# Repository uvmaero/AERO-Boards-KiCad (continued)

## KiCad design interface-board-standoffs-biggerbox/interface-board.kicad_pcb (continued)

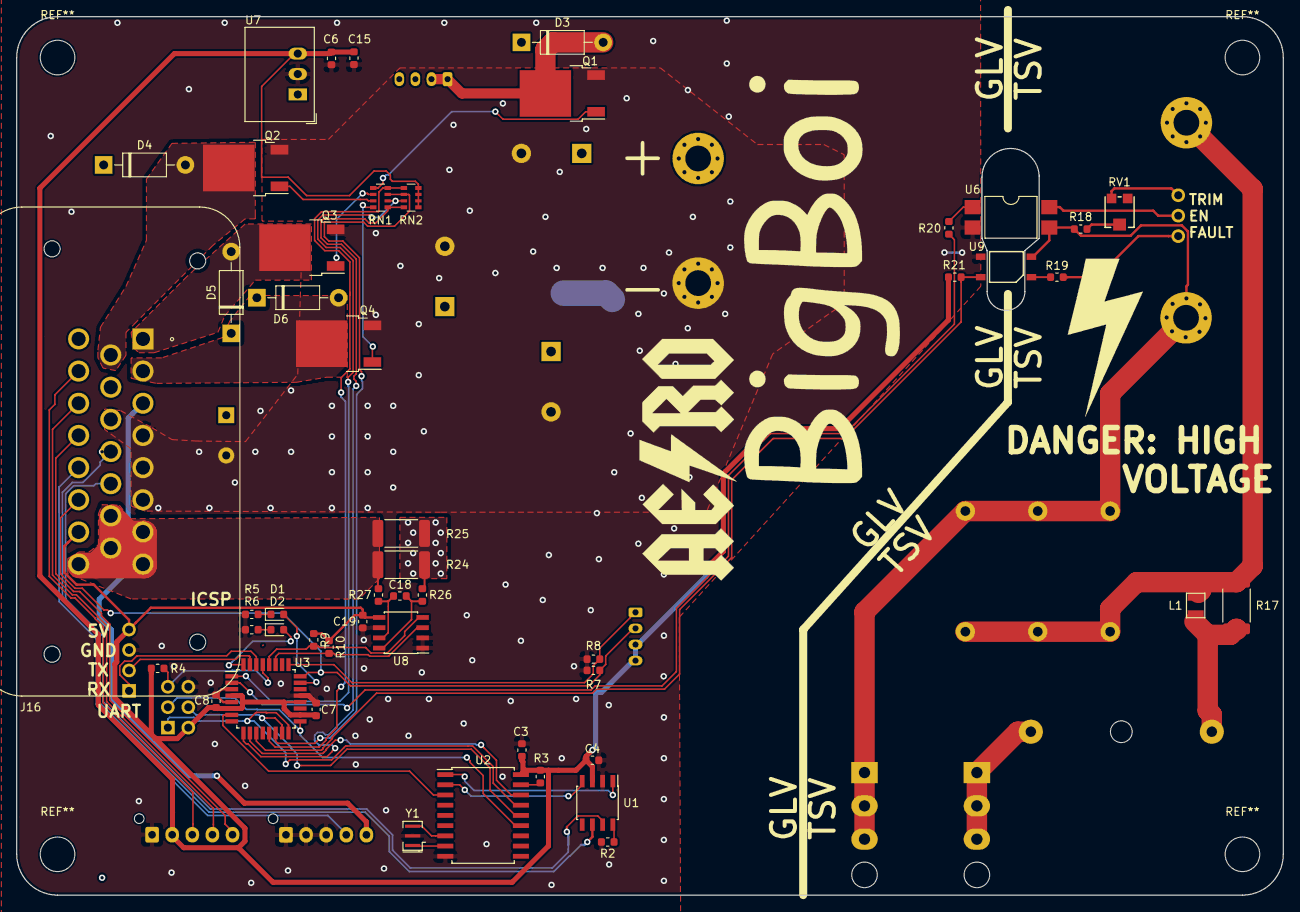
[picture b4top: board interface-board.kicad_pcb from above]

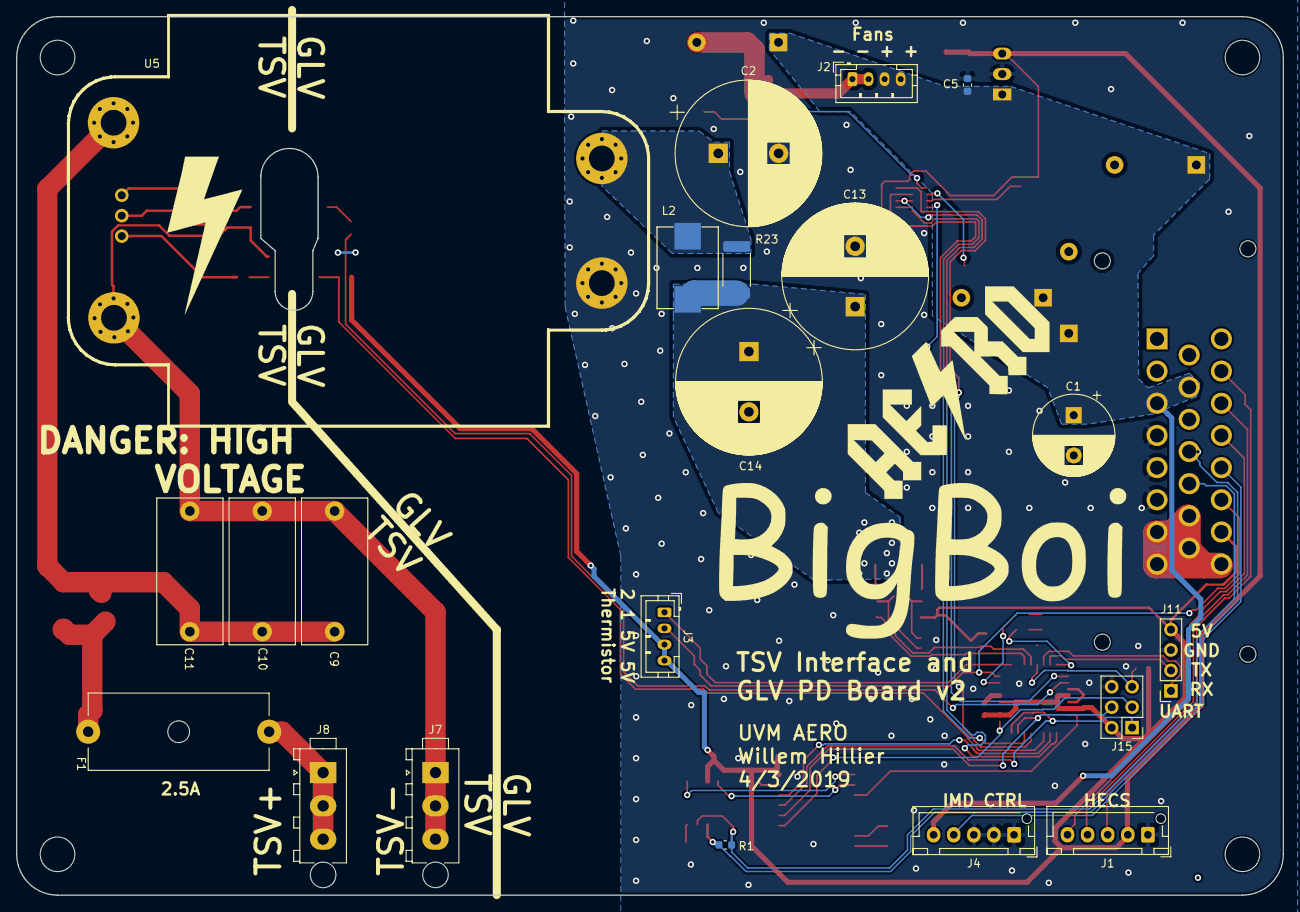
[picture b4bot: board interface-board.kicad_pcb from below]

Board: 2 copper layers, 157.5 x 109.2 mm, 70 parts (21 on the bottom side), 60 nets.

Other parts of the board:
C1: 470uF; CP_Radial_D10.0mm_P5.00mm
C2, C13: 4700uF; CP_Radial_D18.0mm_P7.50mm
R9, R10: 10k; R_0603_1608Metric

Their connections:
+5V: R9.1, R10.1; also elsewhere on the board
+12V: C1.1; also elsewhere on the board
/Main/sheet5C830478/12V_OUT: C13.1; also elsewhere on the board
GND: C1.2, C2.2, C13.2; also elsewhere on the board
unnamed 39: C2.1; also elsewhere on the board
SCL: R9.2; also elsewhere on the board
SDA: R10.2; also elsewhere on the board

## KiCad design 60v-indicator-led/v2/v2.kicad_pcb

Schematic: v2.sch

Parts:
D1: RED_LED; LPA-C011301S-x LED 0805 LIGHT PIPE SINGLE VERT SMD
J1, J2: Conn_01x02; TE_MATE-N-LOK_1-770866-x_1x02_P4.14mm_Vertical
R1, R2, R3, R4, R5, R6, R7, R8, R9, R10: 1k; R_0805_2012Metric

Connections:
unnamed: D1.1 (K), R10.1
unnamed: D1.2 (A), R9.1
unnamed: J1.1, J1.2, R1.2
unnamed: J2.1, J2.2, R2.2
unnamed: R1.1, R3.2
unnamed: R2.1, R4.2
unnamed: R3.1, R5.2
unnamed: R4.1, R6.2
unnamed: R5.1, R7.2
unnamed: R6.1, R8.2
unnamed: R7.1, R9.2
unnamed: R8.1, R10.2

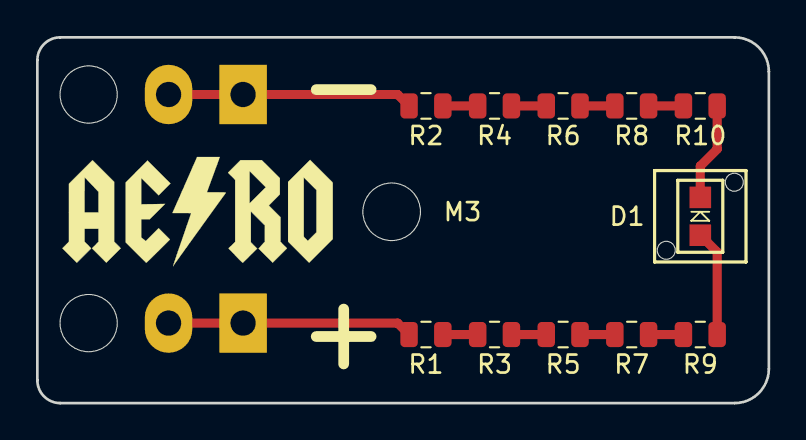
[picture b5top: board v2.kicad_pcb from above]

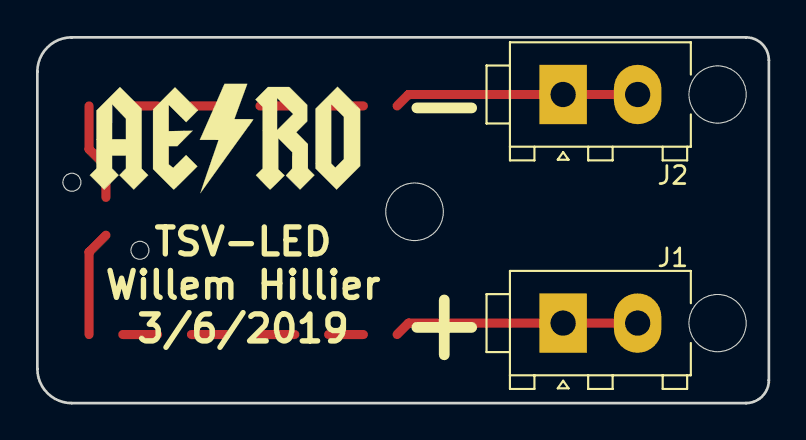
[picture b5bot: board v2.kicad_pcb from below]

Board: 2 copper layers, 40.6 x 20.3 mm, 14 parts (2 on the bottom side), 12 nets.

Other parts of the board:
M3: MountingHole_3.2mm_M3_DIN965

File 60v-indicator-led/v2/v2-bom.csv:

"Id";"Designator";"Package";"Quantity";"Designation";"Supplier and ref";
1;"G***,G***";"AERO_Logo_15x6mm";2;"LOGO";;;
2;"D1";"LPA-C011301S-x LED 0805 LIGHT PIPE SINGLE VERT SMD";1;"RED_LED";;;
3;"R1,R2,R3,R4,R5,R6,R7,R8,R9,R10";"R_0805_2012Metric";10;"1k";;;
4;"M3";"MountingHole_3.2mm_M3_DIN965";1;"MountingHole_3.2mm_M3_DIN965";;;
5;"J1,J2";"TE_MATE-N-LOK_1-770866-x_1x02_P4.14mm_Vertical";2;"Conn_01x02";;;

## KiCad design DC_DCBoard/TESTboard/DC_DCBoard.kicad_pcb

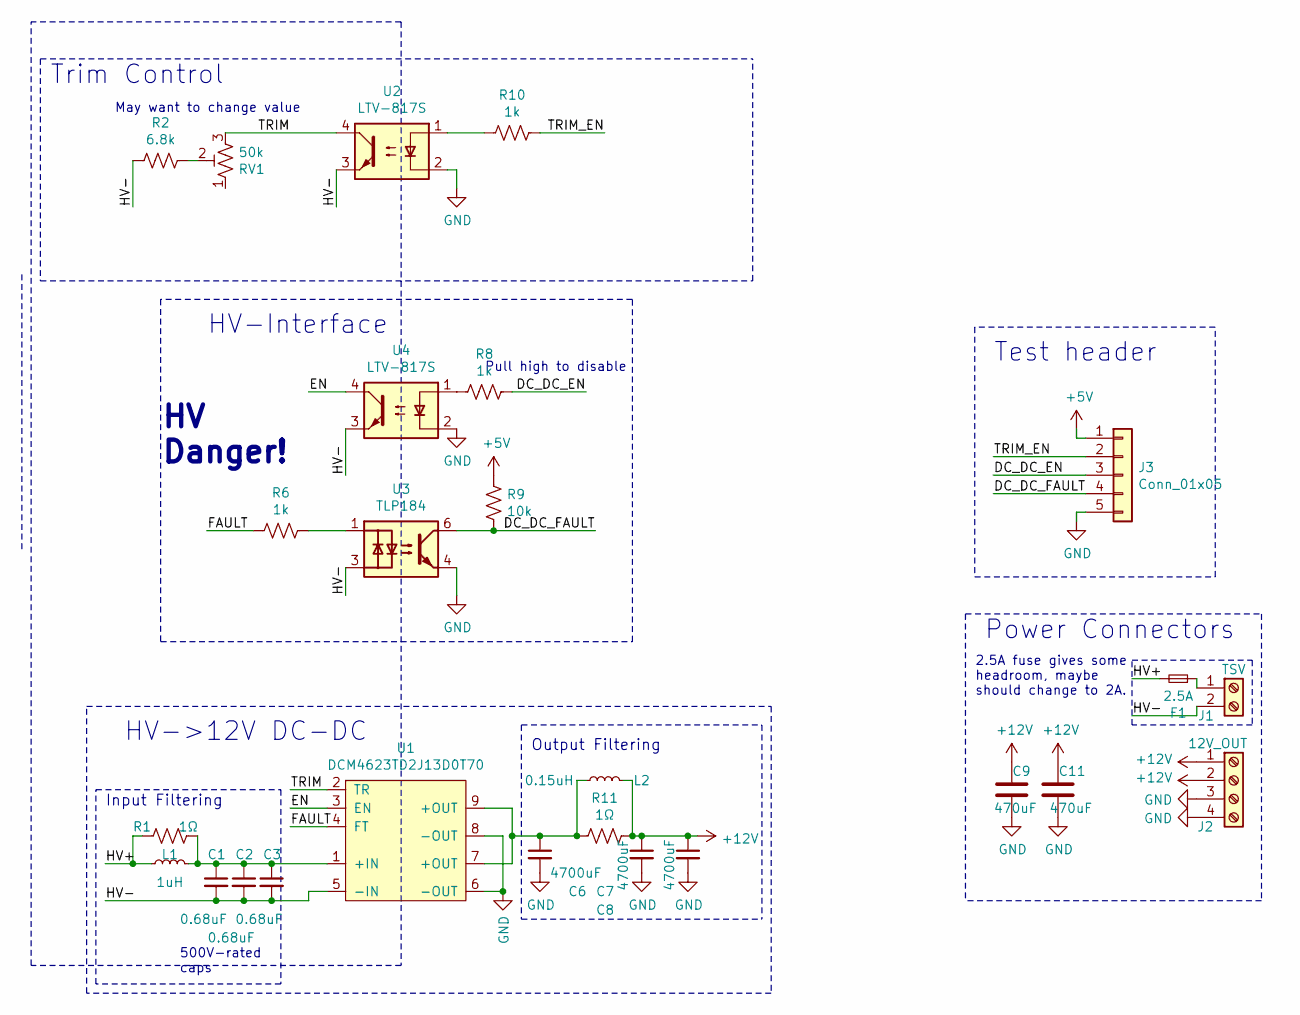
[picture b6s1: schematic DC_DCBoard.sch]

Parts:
C1, C2, C3: 0.68uF; C_Rect_L18.0mm_W8.0mm_P15.00mm_FKS3_FKP3
C6, C7, C8: 4700uF; CP_Radial_D18.0mm_P7.50mm
C9, C11: 470uF; CP_Radial_D10.0mm_P5.00mm
F1: 2.5A; Fuseholder_Cylinder-5x20mm_Schurter_0031_8201_Horizontal_Op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
J1: TSV; TerminalBlock_MetzConnect_Type067_RT01902HDWC_1x02_P10.00mm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
J2: 12V_OUT; TerminalBlock_MetzConnect_Type067_RT01904HDWC_1x04_P10.00mm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
J3: Conn_01x05; PinHeader_1x05_P2.54mm_Vertical
L1: 1uH; Murata_DFE252012P_Inductor
L2: 0.15uH; PA2607
R1, R11: 1Ω; R_2512_6332Metric
R2: 6.8k; R_0603_1608Metric
R6, R8, R10: 1k; R_0603_1608Metric
R9: 10k; R_0603_1608Metric
RV1: 50k; TC33X-503ECT-ND
U1: DCM4623TD2J13D0T70; DCM4623TD2J13D0T70 w_landpattern
U2, U4: LTV-817S; SMDIP-4_W9.53mm
U3: TLP184; TLP182

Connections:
+5V: J3.1, R9.2
+12V: C7.1, C8.1, C9.1, C11.1, J2.1, J2.2, L2.2, R11.1
/DC_DC_EN: J3.3, R8.1
/DC_DC_FAULT: J3.4, R9.1, U3.6
/EN: U1.3 (EN), U4.4
/FAULT: R6.2, U1.4 (FT)
/HV+: F1.2, L1.1, R1.2
/HV-: C1.2, C2.2, C3.2, J1.2, R2.2, U1.5 (-IN), U2.3, U3.3, U4.3
/TRIM: RV1.3, U1.2 (TR), U2.4
/TRIM_EN: J3.2, R10.1
GND: C6.2, C7.2, C8.2, C9.2, C11.2, J2.3, J2.4, J3.5, U1.6 (-OUT), U1.8 (-OUT), U2.2, U3.4, U4.2
unnamed: C1.1, C2.1, C3.1, L1.2, R1.1, U1.1 (+IN)
unnamed: C6.1, L2.1, R11.2, U1.7 (+OUT), U1.9 (+OUT)
unnamed: F1.1, J1.1
unnamed: R2.1, RV1.2
unnamed: R6.1, U3.1
unnamed: R8.2, U4.1
unnamed: R10.2, U2.1

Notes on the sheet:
500V-rated caps
2.5A fuse gives some headroom, maybe should change to 2A.
Input Filtering
Trim Control
Pull high to disable
Power Connectors
HV->12V DC-DC
HV-Interface
HV Danger!
Output Filtering
May want to change value
Test header

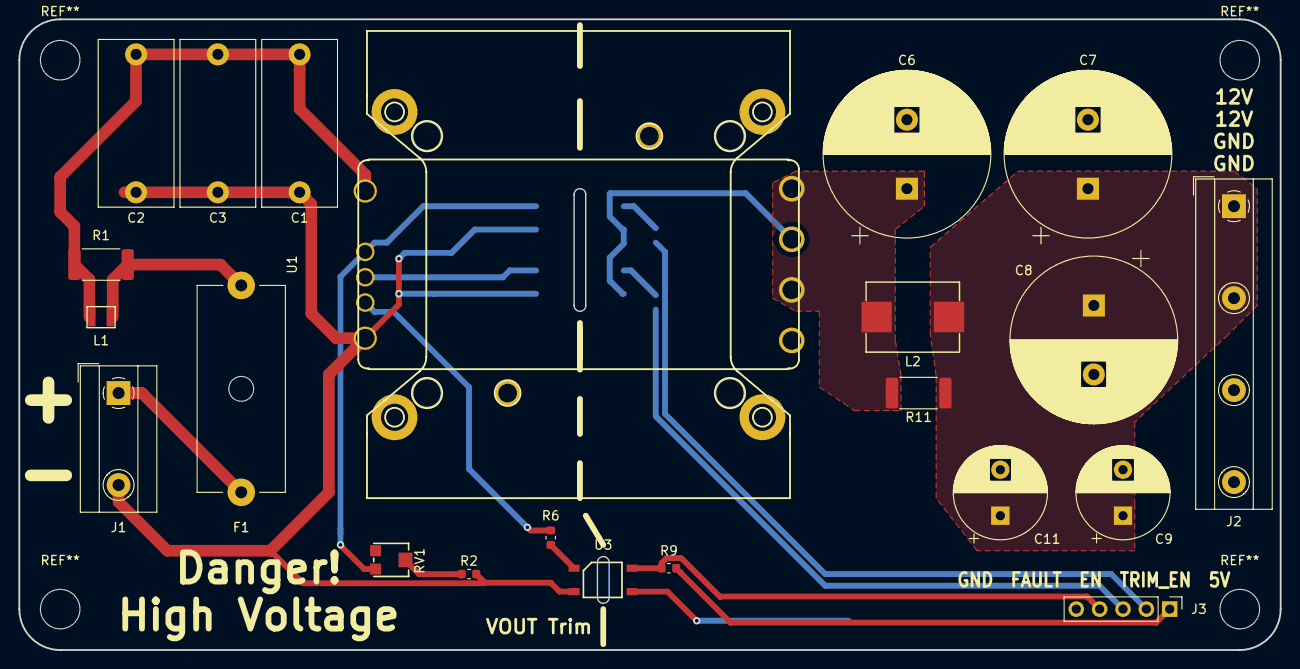
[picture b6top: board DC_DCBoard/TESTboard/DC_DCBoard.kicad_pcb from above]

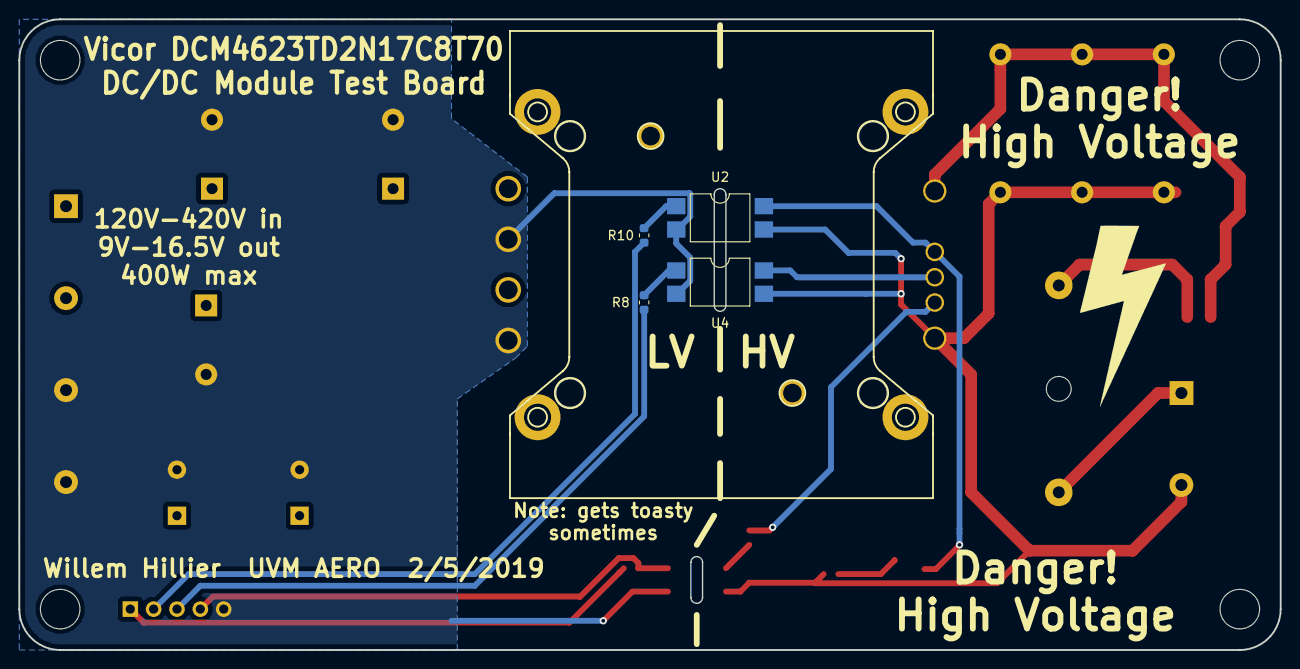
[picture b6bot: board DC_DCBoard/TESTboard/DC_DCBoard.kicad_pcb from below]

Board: 2 copper layers, 137.2 x 68.6 mm, 26 parts (4 on the bottom side), 18 nets.

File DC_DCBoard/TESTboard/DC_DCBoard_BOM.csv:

"Id";"Designator";"Package";"Quantity";"Designation";"Supplier and ref";
1;"F1";"Fuseholder_Cylinder-5x20mm_Schurter_0031_8201_Horizontal_Open_3d";1;"2.5A";;;
2;"U1";"DCM4623TD2J13D0T70_w_landpattern";1;"DCM4623TD2J13D0T70";;;
3;"REF**,REF**,REF**,REF**";"MountingHole_4.3mm_M4";4;"MountingHole_4.3mm_M4";;;
4;"C1,C2,C3";"C_Rect_L18.0mm_W8.0mm_P15.00mm_FKS3_FKP3";3;"0.68uF";;;
5;"C6,C7,C8";"CP_Radial_D18.0mm_P7.50mm";3;"4700uF";;;
6;"C9,C11";"CP_Radial_D10.0mm_P5.00mm";2;"470uF";;;
7;"J1";"TerminalBlock_MetzConnect_Type067_RT01902HDWC_1x02_P10.00mm_Horizontal";1;"TSV";;;
8;"J2";"TerminalBlock_MetzConnect_Type067_RT01904HDWC_1x04_P10.00mm_Horizontal";1;"12V_OUT";;;
9;"L1";"Murata_DFE252012P_Inductor";1;"1uH";;;
10;"L2";"PA2607";1;"0.15uH";;;
11;"R1,R11";"R_2512_6332Metric";2;"1Ω";;;
12;"R6,R8,R10";"R_0603_1608Metric";3;"1k";;;
13;"R9";"R_0603_1608Metric";1;"10k";;;
14;"U2,U4";"SMDIP-4_W9.53mm";2;"LTV-817S";;;
15;"J3";"PinHeader_1x05_P2.54mm_Vertical";1;"Conn_01x05";;;
16;"R2";"R_0603_1608Metric";1;"6.8k";;;
17;"G***";"hvlightningsymbol";1;"LOGO";;;
18;"RV1";"TC33X-503ECT-ND";1;"50k";;;
19;"U3";"TLP182";1;"TLP184";;;

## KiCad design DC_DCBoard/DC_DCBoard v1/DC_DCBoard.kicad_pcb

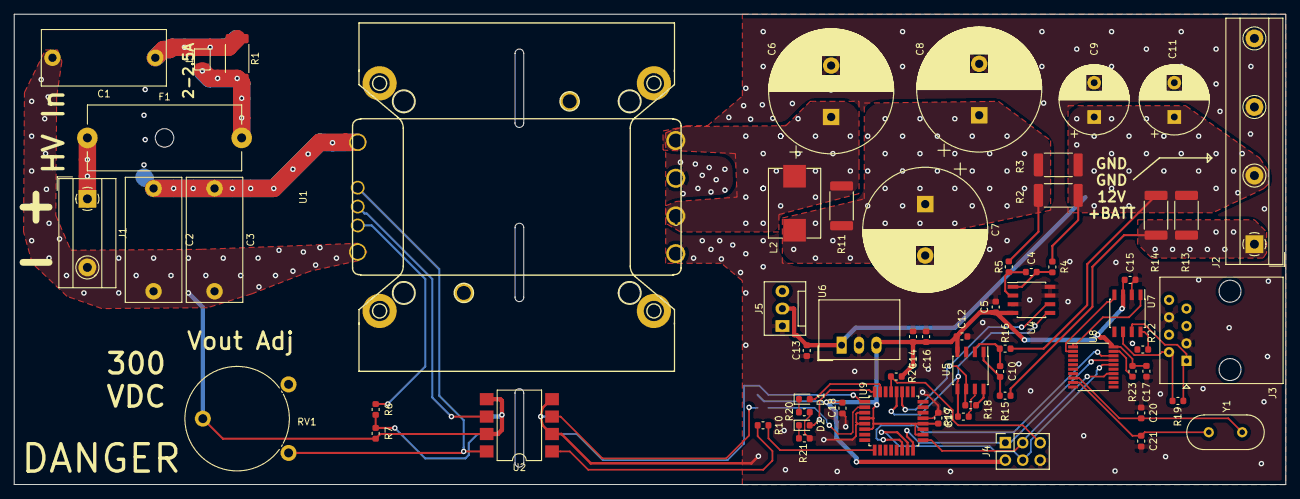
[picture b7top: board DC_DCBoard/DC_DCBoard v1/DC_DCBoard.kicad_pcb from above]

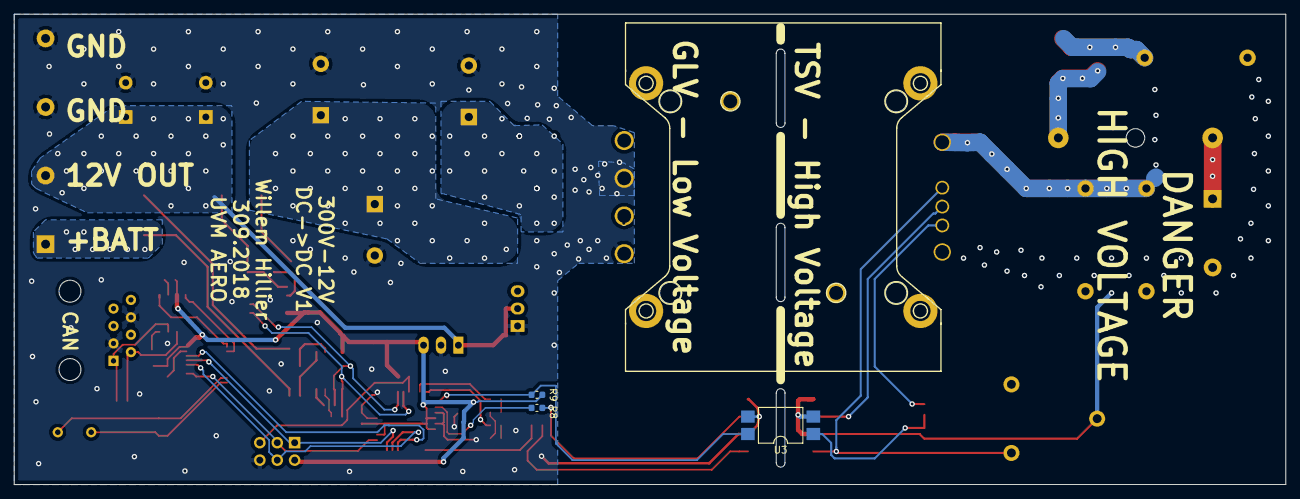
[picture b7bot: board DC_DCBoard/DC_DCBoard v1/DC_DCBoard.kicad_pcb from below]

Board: 2 copper layers, 185.4 x 68.6 mm, 65 parts (3 on the bottom side), 44 nets.

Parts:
C1, C2, C3: 0.68uF; C_Rect_L18.0mm_W8.0mm_P15.00mm_FKS3_FKP3
C4, C5, C10, C12, C14, C15, C17, C18, C19: 0.1uF; C_0603_1608Metric
C6, C7, C8: 4700uF; CP_Radial_D18.0mm_P7.50mm
C9, C11: 470uF; CP_Radial_D10.0mm_P5.00mm
C13, C16: 10uF; C_0603_1608Metric
C20, C21: 22pF; C_0603_1608Metric
D1, D2: LED; LED_0603_1608Metric
F1: 2.5A; Fuseholder_Cylinder-5x20mm_Schurter_0031_8201_Horizontal_Op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
J1: TSV; TerminalBlock_MetzConnect_Type067_RT01902HDWC_1x02_P10.00mm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
J2: 12V_OUT; TerminalBlock_MetzConnect_Type067_RT01904HDWC_1x04_P10.00mm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
J3: RJ45; RJ45_Amphenol_54602-x08_Horizontal
J4: Conn_02x03_Odd_Even; PinSocket_2x03_P2.54mm_Vertical
J5: FAN; FanPinHeader_1x03_P2.54mm_Vertical
L1: 1uH; Murata_DFE252012P_Inductor
L2: 0.15uH; PA2607
R1, R11: 1Ω; R_2512_6332Metric
R2, R3, R13, R14: 0.02; R_2512_6332Metric
R4, R5, R15, R16: 10; R_0603_1608Metric
R6, R8, R10, R20, R21: 1k; R_0603_1608Metric
R7: 50k; R_0603_1608Metric
R9, R17, R18, R22, R23, R24: 10k; R_0603_1608Metric
R19: R_US; R_0603_1608Metric
RV1: 5k; Potentiometer_Piher_PT-15-V02_Vertical
U1: DCM4623TD2J13D0T70; DCM4623TD2J13D0T70 w_landpattern
U2: LTV-827S; SMDIP-8_W9.53mm
U3: LTV-817S; SMDIP-4_W9.53mm
U4, U5: INA219; SOIC-8_3.9x4.9mm_P1.27mm
U6: R-78E5.0-0.5; Converter_DCDC_RECOM_R-78E-0.5_THT
U7: MCP2551-I-SN; SOIC-8_3.9x4.9mm_P1.27mm
U8: MCP2515-IST; TSSOP-20_4.4x6.5mm_P0.65mm
U9: ATmega328P-AU; TQFP-32_7x7mm_P0.8mm
Y1: 16MHz; Crystal_HC49-U_Vertical

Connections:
+5V: C5.2, C12.2, C14.1, C15.1, C16.1, C17.1, C18.1, C19.1, J4.2, R9.2, R23.1, R24.1, U4.4, U5.4, U6.3, U7.3, U8.20, U9.4, U9.6, U9.18, U9.20
+12V: C9.1, C11.1, C13.1, J2.2, J5.2, R2.2, R3.2, R4.2, R13.1, R14.1, R16.2, U6.1
+BATT: J2.1, R13.2, R14.2, R15.2
/12V_UNMETERED: C7.1, C8.1, L2.2, R2.1, R3.1, R5.2, R11.1
/D10: U8.18, U9.14
/DC_DC_EN: R8.1, U9.2
/DC_DC_FAULT: R9.1, U3.4, U9.1
/EN: U1.3, U2.6
/FAULT: R6.2, U1.4
/HV+: F1.2, L1.1, R1.2
/HV-: C1.2, C2.2, C3.2, J1.2, R7.2, RV1.2, U1.5, U2.5, U2.7, U3.2
/LED1: D1.2, U9.31
/LED2: D2.2, U9.32
/MISO: J4.1, U8.17, U9.16
/MOSI: J4.4, U8.16, U9.15
/RESET: J4.5, R24.2, U9.29
/SCK: J4.3, U8.14, U9.17
/SCL: R17.1, U4.5, U5.5, U9.28
/SDA: R18.1, U4.6, U5.6, U9.27
/TRIM: RV1.3, U1.2, U2.8
/TRIM_EN: R10.1, U9.9
GND: C5.1, C6.2, C7.2, C8.2, C9.2, C11.2, C12.1, C13.2, C14.2, C15.2, C16.2, C17.2, C18.2, C19.2, C20.2, C21.2, J2.3, J2.4, J3.3, J3.6, J4.6, J5.1, R20.1, R21.1, R22.2, U1.6, U1.8, U2.2, U2.4, U3.3, U4.3, U4.7, U4.8, U5.3, U6.2, U7.2, U8.10, U9.3, U9.5, U9.21
unnamed: C1.1, C2.1, C3.1, L1.2, R1.1, U1.1
unnamed: C4.1, R4.1, U4.1
unnamed: C4.2, R5.1, U4.2
unnamed: C6.1, L2.1, R11.2, U1.7, U1.9
unnamed: C10.1, R15.1, U5.1
unnamed: C10.2, R16.1, U5.2
unnamed: C20.1, U8.8, Y1.1
unnamed: C21.1, U8.9, Y1.2
unnamed: D1.1, R20.2
unnamed: D2.1, R21.2
unnamed: F1.1, J1.1
unnamed: J3.1, R19.1, U7.7
unnamed: J3.2, R19.2, U7.6
unnamed: R6.1, R7.1, U3.1
unnamed: R8.2, U2.3
unnamed: R10.2, U2.1
unnamed: R17.2, U5.7
unnamed: R18.2, U5.8
unnamed: R22.1, U7.8
unnamed: R23.2, U8.19
unnamed: U7.1, U8.1
unnamed: U7.4, U8.2

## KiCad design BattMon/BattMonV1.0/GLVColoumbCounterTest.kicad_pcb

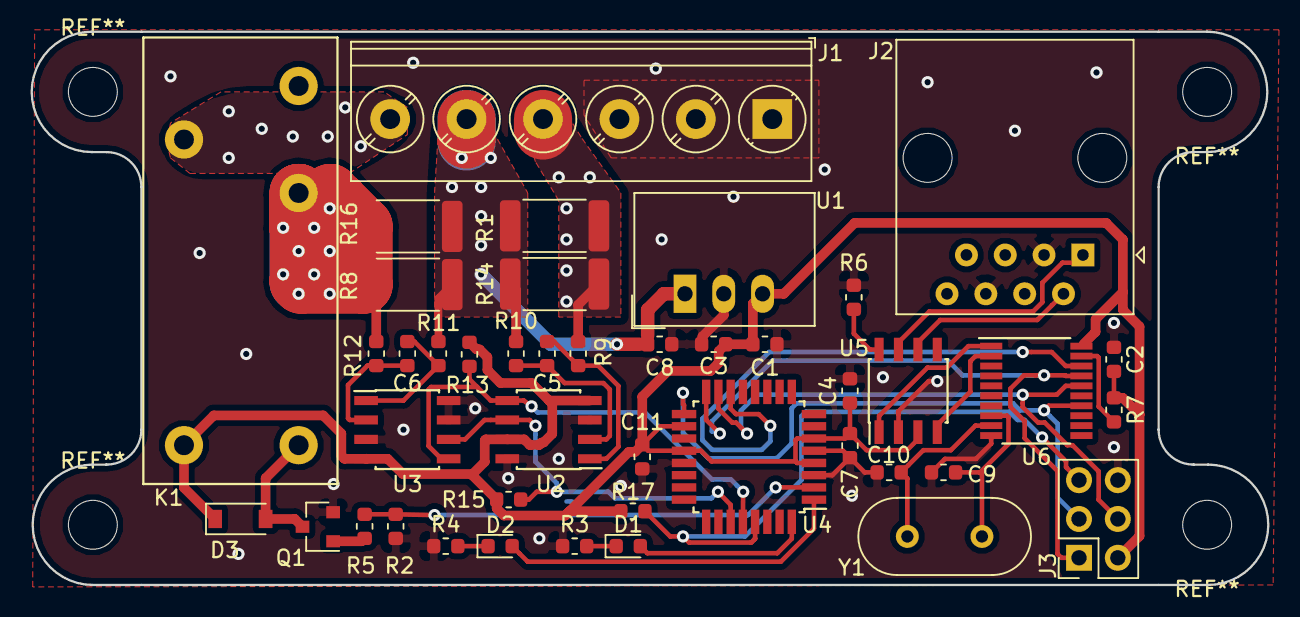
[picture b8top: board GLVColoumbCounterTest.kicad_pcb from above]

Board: 2 copper layers, 80.9 x 36.2 mm, 43 parts (0 on the bottom side), 32 nets.

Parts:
C1, C2, C4, C5, C6, C7, C11: 0.1uF; C_0603_1608Metric
C3, C8: 10uF; C_0603_1608Metric
C9, C10: 22pF; C_0603_1608Metric
D1, D2: LED; LED_0603_1608Metric
D3: 1N4148; D_SOD-123
J1: 12V_INTERFACE; TerminalBlock_Phoenix_PT-1,5-6-5.0-H_1x06_P5.00mm_Horizontal
J2: RJ45; RJ45_Amphenol_54602-x08_Horizontal
J3: Conn_02x03_Odd_Even; PinSocket_2x03_P2.54mm_Vertical
K1: G5V-1; G2RL
Q1: MMBT222A; SOT-23
R1, R8, R14, R16: 0.02; R_2512_6332Metric
R2: 100k; R_0603_1608Metric
R3, R4, R5: 1k; R_0603_1608Metric
R6, R7, R15, R17: 10k; R_0603_1608Metric
R9, R10, R11, R12: 10; R_0603_1608Metric
R13: 10K; R_0603_1608Metric
U1: R-78E5.0-0.5; Converter_DCDC_RECOM_R-78E-0.5_THT
U2, U3: INA219; SOIC-8_3.9x4.9mm_P1.27mm
U4: ATmega328P-AU; TQFP-32_7x7mm_P0.8mm
U5: MCP2551-I-SN; SOIC-8_3.9x4.9mm_P1.27mm
U6: MCP2515-IST; TSSOP-20_4.4x6.5mm_P0.65mm
Y1: 8MHz; Crystal_HC49-U_Vertical

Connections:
+5V: C1.1, C2.1, C3.1, C4.1, C7.1, C11.1, D3.1, J3.2, K1.2, R7.1, R13.1, R15.1, R17.1, U1.3, U2.4, U2.7, U3.4, U4.4, U4.6, U4.18, U4.20, U5.3, U6.20
+12V: C8.1, J1.5, R1.1, R8.2, R10.2, R11.2, R14.1, R16.2, U1.1
+BATT: K1.1, R8.1, R12.2, R16.1
/D10: U4.14, U6.18
/LED1: D1.2, U4.32
/LED2: D2.2, U4.1
/LOAD: J1.4, R1.2, R9.2, R14.2
/MISO: J3.1, U4.16, U6.17
/MOSI: J3.4, U4.15, U6.16
/RELAY_CTRL: R2.1, R5.2, U4.2
/RESET: J3.5, R17.2, U4.29
/SCK: J3.3, U4.17, U6.14
/SCL: R13.2, U2.5, U3.5, U4.28
/SDA: R15.2, U2.6, U3.6, U4.27
GND: C1.2, C2.2, C3.2, C4.2, C7.2, C8.2, C9.2, C10.2, C11.2, J1.1, J1.2, J1.3, J2.3, J2.6, J3.6, Q1.2, R2.2, R3.1, R4.1, R6.2, U1.2, U2.3, U2.8, U3.3, U3.7, U3.8, U4.3, U4.5, U4.21, U5.2, U6.10
unnamed: C5.1, R9.1, U2.1
unnamed: C5.2, R10.1, U2.2
unnamed: C6.1, R11.1, U3.1
unnamed: C6.2, R12.1, U3.2
unnamed: C9.1, U6.8, Y1.1
unnamed: C10.1, U6.9, Y1.2
unnamed: D1.1, R3.2
unnamed: D2.1, R4.2
unnamed: D3.2, K1.9, Q1.3
unnamed: J1.6, K1.5
unnamed: J2.1, U5.7
unnamed: J2.2, U5.6
unnamed: Q1.1, R5.1
unnamed: R6.1, U5.8
unnamed: R7.2, U6.19
unnamed: U5.1, U6.1
unnamed: U5.4, U6.2

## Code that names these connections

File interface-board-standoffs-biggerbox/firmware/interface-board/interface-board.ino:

#include <Adafruit_INA219.h>
#include <SPI.h>
#include "mcp_can.h"

//CAN ID defines
#define ID_RMC_TEMPS1 0xA0
#define ID_RMC_TEMPS2 0xA1
#define ID_RMC_TEMPS3 0xA2
#define ID_DASH_COOLING_EN 0x6F
#define ID_TEST_INTERFACE_BOARD 0x70

//NTC Constants
#define THERMISTOR_B_VAL 3380
#define NTC_R_ROOM 10000
#define NTC_T_ROOM 25
#define NTC_BETA 3380
#define R_DIVIDER 10000
#define DMAX 1023

//How often to send CAN heartbeat/status
#define HEARTBEAT_INTERVAL 200

//Pin defines
#define SPI_CAN_CS   6
#define LED1         14      //blue led
#define LED2         2       //green led
#define FAN0         9       //Internal fan header
#define FAN1         10      //Radiator fans
#define FAN2         3       //Cooling pump
#define FAN3         5       //Nothing yet
#define NTC1         A1
#define NTC2         A2
#define DC_DC_EN     4
#define DC_DC_FAULT  7
#define DC_DC_TR_EN  8

MCP_CAN CAN(SPI_CAN_CS);     // Set CS pin

Adafruit_INA219 ina219;

bool coolingEnabled;
int16_t RMCTemps[11];       //Motor controller temps, equivilent to the following:

uint32_t lastheartbeatTime;
/*
  int RMCTempA     = 0;  //IGBT phase A
  int RMCTempB     = 0;  //IGBT phase B
  int RMCTempC     = 0;  //IGBT phase C
  int RMCTempGDB   = 0;  //gate driver board
  int RMCTempCB    = 0;  //control board
  int RMCTempRTD1  = 0;  //RTD input 1
  int RMCTempRTD2  = 0;  //RTD input 2
  int RMCTempRTD3  = 0;  //RTD input 3
  int RMCTempRTD4  = 0;  //RTD input 4
  int RMCTempRTD5  = 0;  //RTD input 5
  int RMCTempMotor = 0;  //filtered temp value from motor temp sensor
*/

void setup() {
  pinMode(LED1, OUTPUT);
  pinMode(LED2, OUTPUT);
  pinMode(FAN2, OUTPUT);
  pinMode(FAN0, OUTPUT);
  pinMode(FAN1, OUTPUT);
  pinMode(FAN2, OUTPUT);
  pinMode(FAN3, OUTPUT);
  pinMode(DC_DC_EN, OUTPUT);
  pinMode(DC_DC_TR_EN, OUTPUT);

  Serial.begin(115200);

  lastheartbeatTime = millis(); //Used for sending out status/temps/voltage/current/heartbeat over CAN on a regular interval

  ina219.begin();

  while (CAN_OK != CAN.begin(CAN_500KBPS)) { //Check we can talk to CAN
    Serial.println("CAN BUS Shield init fail");
    Serial.println("Init CAN BUS Shield again");
    delay(100);
  }
  Serial.println("CAN BUS Shield init ok!");
}

void testRoutine(){
//Test routine
  delay(1000);

  //Internal fans
  Serial.println("Testing internal fans.");
  analogWrite(FAN0, 255);
  delay(1000);
  analogWrite(FAN0, 0);

  //Radiator fans
  Serial.println("Testing radiator fans.");
  analogWrite(FAN1, 255);
  delay(1000);
  analogWrite(FAN1, 0);

  //Cooling pump
  Serial.println("Testing cooling pump.");
  delay(1000);
  analogWrite(FAN2, 0);

  //NTCs
  Serial.println("Testing NTCs.");
  Serial.print("NTC 1 Temp (deg C): ");
  Serial.println(calculateTemperatureC(analogRead(NTC1)));
  Serial.print("NTC 2 Temp (deg C): ");
  Serial.println(calculateTemperatureC(analogRead(NTC2)));

  //LEDs
  Serial.println("Testing LEDs.");
  Serial.println("LED1");
  digitalWrite(LED1, HIGH);
  Serial.println("LED2");
  digitalWrite(LED2, HIGH);
  
}

float calculateTemperatureC(float adcReading) {
  float NTCResistance = R_DIVIDER * ((DMAX / adcReading) - 1);
  float tKelvin = 1 / (NTC_T_ROOM + NTC_BETA * log(NTC_R_ROOM / NTCResistance));
  return tKelvin + 273.15;
}

void updateFansFromTemps() {
  //Print temps
  for (int i = 0; i < 11; i++) {
    Serial.println(RMCTemps[i]);
  }

  //Find max temp
  int16_t maxTemp = 0;
  for (int i = 0; i < 12; i++) {
    if (maxTemp < RMCTemps[i]) {
      maxTemp = RMCTemps[i];
    }
  }

  //Radiator fan control
  analogWrite(FAN1, map(maxTemp, 20, 30, 0, 255)); //TODO: Check mapping

  //Pump control with deadband
  if (maxTemp > 23) { //TODO: Check mapping
    digitalWrite(FAN2, 0);
  }
  else if (maxTemp < 20) {
    digitalWrite(FAN2, 1);
  }

  //Local fan control
  float NTC1Temp = calculateTemperatureC(analogRead(NTC1));
  analogWrite(FAN0, map(NTC1Temp, 0, 1023, 30, 255)); //TODO: Change mapping, may need to max/min this to avoid weird overflow-type issues on analogWrite
}

void reportVoltageCurrentTemps() {
  uint16_t voltage_mV = ina219.getBusVoltage_V();
  uint16_t current_mA = ina219.getCurrent_mA();

  //Example CAN message data: 0x3D   0x35   0x5B   0x57   0x00      0x00      0x00      0x00
  //                          V_LSB  V_MSB  A_LSB  A_MSB  NTC1_LSB  NTC1_MSB  NTC2_LSB  NTC2_MSB
  //Here, 13.629V and 22.363A
  unsigned char bufToSend[8] = {0, 0, 0, 0, 0, 0, 0, 0};
  bufToSend[0] = voltage_mV;
  bufToSend[1] = voltage_mV << 256;
  bufToSend[2] = current_mA;
  bufToSend[3] = current_mA << 256;

  //Report internal temps on CAN
  //TODO: Map values to temp properly
  float NTC1Temp = calculateTemperatureC(analogRead(NTC1));
  float NTC2Temp = calculateTemperatureC(analogRead(NTC2));
//  bufToSend[4] =
//    bufToSend[5]
//    bufToSend[6]
//    bufToSend[7]

    CAN.sendMsgBuf(0x68, 0, 8, bufToSend);
}

void filterCan(unsigned long canId, unsigned char buf[8]) { //Decides what to do with CAN data
  switch (canId) {
    case ID_RMC_TEMPS1:
      for (int i = 0; i < 4; i++) {
        RMCTemps[i] = (buf[2 * i + 1] << 8) + buf[2 * i]; //Place temps into RMCTemps
      }
      //Serial.println("Recieved temps1");
      break;
    case ID_RMC_TEMPS2:
      for (int i = 0; i < 4; i++) {
        RMCTemps[i + 4] = (buf[2 * i + 1] << 8) + buf[2 * i];  //Place temps into RMCTemps
      }
      break;
    case ID_RMC_TEMPS3:
      for (int i = 0; i < 3; i++) {
        RMCTemps[i + 8] = (buf[2 * i + 1] << 8) + buf[2 * i];  //Place temps into RMCTemps
      }
      break;
    //TODO: Implement dash cooling enable/disable
    case ID_DASH_COOLING_EN:
      Serial.println("Received cooling_en status");
      break;
    case ID_TEST_INTERFACE_BOARD:
      testRoutine();
    default:
      Serial.println("Received an unknown CAN ID.");
      break;
  }
}

void loop() {
  unsigned char len = 0;
  unsigned char buf[8];

  if (CAN_MSGAVAIL == CAN.checkReceive()) {   // check if data coming
    CAN.readMsgBuf(&len, buf);    // read data,  len: data length, buf: data buf

    filterCan(CAN.getCanId(), buf);
    updateFansFromTemps(); //Updates all cooling fan speeds + pump enable according to temps
  }

  //TODO:
  //Check for DC/DC fault
  //If fault, then:
  //turn DC/DC off and back on
  //Report on CAN

  if (millis() > lastheartbeatTime + HEARTBEAT_INTERVAL) {
    lastheartbeatTime = millis();
    reportVoltageCurrentTemps();
    //TODO: checkAndReportDCDCStatus();
  }
}

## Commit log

2018-11-25 Uploaded files
2018-11-25 Updated Readme and license.
2018-11-25 Updated pics
2018-11-25 Updated more pics
2019-01-25 Created interface-board
2019-01-25 Lots of interface-board layout done
2019-01-25 interface-board getting there schematic-wise.
2019-01-25 schematic almost done maybe hopefully
2019-01-25 more interface-board
2019-01-26 Beginnings of board layout of interface-board
2019-01-27 Updated main connector and pinout
2019-01-28 Added IMD LV connector
2019-01-29 Fixed more shit
2019-01-29 Created PDF schematic for interface-board
2019-02-05 did some stuff
2019-02-06 Made DC/DC test board
2019-02-06 Made PDF schematic of DC/DC test board
2019-02-06 Fixed pot value on test board
2019-02-06 updated footprints
2019-02-06 updated test-board
2019-02-06 Footprints centralized now
2019-02-09 Getting there with layout of big board...
2019-02-09 Interface-board largely routed
2019-02-10 Fully routed, added blinky DC/DC, added silkscreen labels, bumped 5V traces up to 0.025"
2019-02-12 Cleaned up 3d models
2019-02-13 Updated 3d footprints on testboard
2019-02-15 Added board images for interface-board
2019-02-22 Made LED indicator.
2019-02-22 dunno
2019-03-05 Put Vicor on a removable module
2019-03-06 Board probably ready to ship.
2019-03-07 Added parts to custom-footprints
2019-03-07 Made lots of gerbers, shipped boards.
    Also, re-routed interface-board to be 8/8mil minimum spacing.
2019-03-17 made iBom for assembly and current schematic pdf
2019-03-27 Beginning of interface-board, moved around interface-board files for better organization
2019-03-28 Fixed firmware folder
2019-03-30 Made BOM etc for 60v-indicator-led
2019-03-30 Added more images of boards
2019-04-04 Made rev1.1 of interface-board
    Added i2c pullups, fixed chip pinout, added isolation slot, removed secondary DC/DC converter
2019-04-05 Shipped interface-board-standoffs-biggerbox
2019-04-15 Cleaned up drawings.user laser on interface-board, and made iBom for assembly.
2019-04-20 Fully working interface-board firmware, fixed wrong polarity on vicor-socket
2019-04-26 Fixed lots of stuff for interface-board. It works now.
    Still need to implement brake light control and debug cooling switch logic because it don't work
2019-04-28 Added brakelight control code
2019-05-08 Started making TSAL-driver PCB
2019-06-25 Drew fet inverter
2019-07-10 More work on TSAL-driver.
    TODO: Get actual values in for both 555 circuits.
2019-07-17 TODO: update values for 555 blinker
2019-08-16 Beginning of can-game-controller
    An interface to drive a simulator with the real car.
2019-08-18 Finished USB CANBUS game controller
    Will allow us to use the car as a game controller for a simulator
2019-08-27 TSAL-driver board schematic mostly done, just need to double-check
2019-09-10 Added footprints for tsal-driver
2019-09-11 Started laying out TSAL-driver
2019-09-11 Moved capictor
2019-09-12 Organized TSAL-Driver board
2019-09-16 Inputs and Outputs are on Opposite Sides
2019-10-04 New TSAL Schematic
    Schematic complete, on to annotations
2019-10-08 Made Game Controller BOM
2019-10-08 Made KiCad footprints library + added first component
2019-10-08 started choosing footprints
2019-10-09 Finished TSAL-driver
2019-10-09 Cleaned up board, added 3D
2019-10-09 Fixed 3d
2019-10-09 Added 3D for terminals, cleaned up old 3d
2019-10-09 New LDB footprint
    Completed TSAL
2019-10-15 Start work on port panel
2019-10-21 Update libs (add TUSB4020BIPHPR)
2019-10-21 Work on port panel
2019-10-24 Demo Board RGB LED
2019-10-25 Demo Board updated. Ready for Review
2019-11-01 Work on USB Hub
2019-11-10 more port panel
2019-11-11 Updated libs for dash
2019-11-11 added ampseal
2019-11-11 library work
2019-11-11 library work, added logos and 3d for RJ45
2019-11-16 Added 3d
2019-12-10 Firmware for demo board
